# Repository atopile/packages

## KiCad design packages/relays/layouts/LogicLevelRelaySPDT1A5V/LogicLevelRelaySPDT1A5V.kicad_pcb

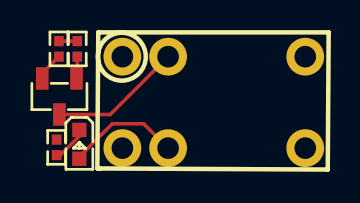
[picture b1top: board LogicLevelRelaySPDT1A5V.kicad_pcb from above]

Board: 2 copper layers, 6 parts (0 on the bottom side), 7 nets.

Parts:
K1: RELAY-TH_G5V-1
LED1: LED0603-RD
Q1: SOT-23-3_L2.9-W1.3-P1.90-LS2.4-BR
R1, R2: 10000Ω; R0402
R3: 4700Ω; R0402

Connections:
anode: K1.2, LED1.2
cathode: LED1.1, R3.1
common: K1.5, K1.6
contacts[1]: K1.9, Q1.3
gate: Q1.1, R2.2
line: R1.1, R2.1
lv: Q1.2, R1.2, R3.2
